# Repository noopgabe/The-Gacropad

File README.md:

# The GacroPad

> 

A six-key macro pad that plugs into a PC as a USB keyboard, with a small OLED for whatever you feel like showing it. Time, stats, whatever. If it doesn't have it, make it.

I made this because I play Roblox. Roblox is very weird. Some games are intense, and some are calmer. If you couldn't tell, I play intensely. I also listen to music. Can you REALLY switch between music and being in the middle of a chase sequence? No. No you can't. This is why I built the GacroPad. I also need macros for some things, limited to, but not excluding:

- Complicated actions 
- Die of Death
- Soundboard

The screen helps in a way because I can see the time when I'm in a heavy chase and I can't hit F11 without getting myself hit in a chase.

---

The repo has two halves: the firmware that runs on the pad, and a GTK4 companion app. The pad is good itself. The companion app is the real business, but the firmware is where all the magic happens. The companion app is cooler, I swear on my life.

## The hardware

It's built around an **ESP32-S3-WROOM-1U**:

- a 1.3" SSD1306 128x64 I2C OLED (the address is probed at boot, so `0x3C` and `0x3D` both work)
- native USB, but \* 2: TinyUSB HID for the keyboard and media keys, and a CDC port for talking to the companion app.

Macros can send ordinary keystrokes, raw HID usages, media keys, text, and delays. They're stored in NVS, so they survive power cycles and reflashes. If that is one of your worries, let them be free!

## Building the firmware

```bash
pio run
```

That gives you `firmware.bin`, which is only the application. A _first_ flash over the ROM bootloader kinda needs the whole thing, so instead run this:

```bash
pio run -t mergedbin
```

That writes `.pio/build/gacropad/gacropad.bin`, which includes the bootloader, partition table, and app, ready to flash at offset `0x0`.

### Flashing

There's buttons. On the PCB. One is BOOT. One is RESET. Hold BOOT, and then hit RESET. After, you can flash it through various ways, but my favorite is esptool. For the sake of time, I will only place that.

```bash
esptool.py --port /dev/ttyUSB0 write_flash 0x0 .pio/build/gacropad/gacropad.bin
```

## The companion app

GTK4, via PyGObject, which means it wants the system Python:

```bash
sudo apt install python3-gi gir1.2-gtk-4.0
pip install -r companion/requirements.txt
cd companion && /usr/bin/python3 main.py
```

A plain venv usually won't have `gi`, which is why we have the `/usr/bin/python3`. The app finds the pad on its own if there's only one, and you should only have one anyway, since 2 is nuts and 3 is a mental health issue.

What it's for:

- Macro editing. Seriously, what else? Click a key to open its editor. Recording captures whatever you do but only while the editor window has focus, because why else? Just write it down on a notepad if you need to remember. This is why it works on Wayland without root. Esc stops. There's a "test fire" button, and presets if you're a baby and you don't like to record.
- OLED modes. `labels` (key names), `clock`, `stats` (CPU and memory), and `live` (two lines of text you control). The live lines are plain text pushed over serial, so anything can be there.

The key buttons push one slot at a time, meanwhile "push all" pushes all six. Of course.

## The serial protocol

Newline-delimited JSON, one request per line, one reply per line. If you're handy, this is maybe useful. _Maybe._ This usually isn't, but if you eventually figure it out, congratulations, you're a nerd.

```
{"cmd":"ping"}
{"cmd":"get","key":0}
{"cmd":"set","key":0,"slot":{"label":"K1","steps":[{"t":"raw","v":104,"hold":40}]}}
{"cmd":"press","key":0}
{"cmd":"oled","mode":"clock"}
{"cmd":"live","clock":"14:32","l1":"hello","l2":"world"}
{"cmd":"stats","cpu":12,"mem":40}
{"cmd":"reset"}
```

Replies always carry `ok`, and an `err` when it's false. The pad also emits unsolicited `{"ev":...}` lines of its own when you press a key.

Macro steps are `delay`, `text`, `media`, `raw`, `key`, `down`, and `up`, where `down` and `up` are for chords, like holding Ctrl and then tapping C.

## CAD files

Well, here's the thing. The case is not done yet. It will be done soon. Trust me, it won't be late. 

## Credits and confessions

Built with [U8g2](https://github.com/olikraus/u8g2) (thank you) and [ArduinoJson](https://github.com/bblanchon/ArduinoJson) (thank you too), and a great deal of beating the hugs out of the ESP32 Arduino HID API until it worked well.

The code comments are better than the actual code, unfortunately. I am not good at programming, or designing, or whatever. If you object, do not.

I have committed many sins (sloth, sloth, sloth, and sloth), and this is unfortunately my penance. This was lazy, but that's fine.

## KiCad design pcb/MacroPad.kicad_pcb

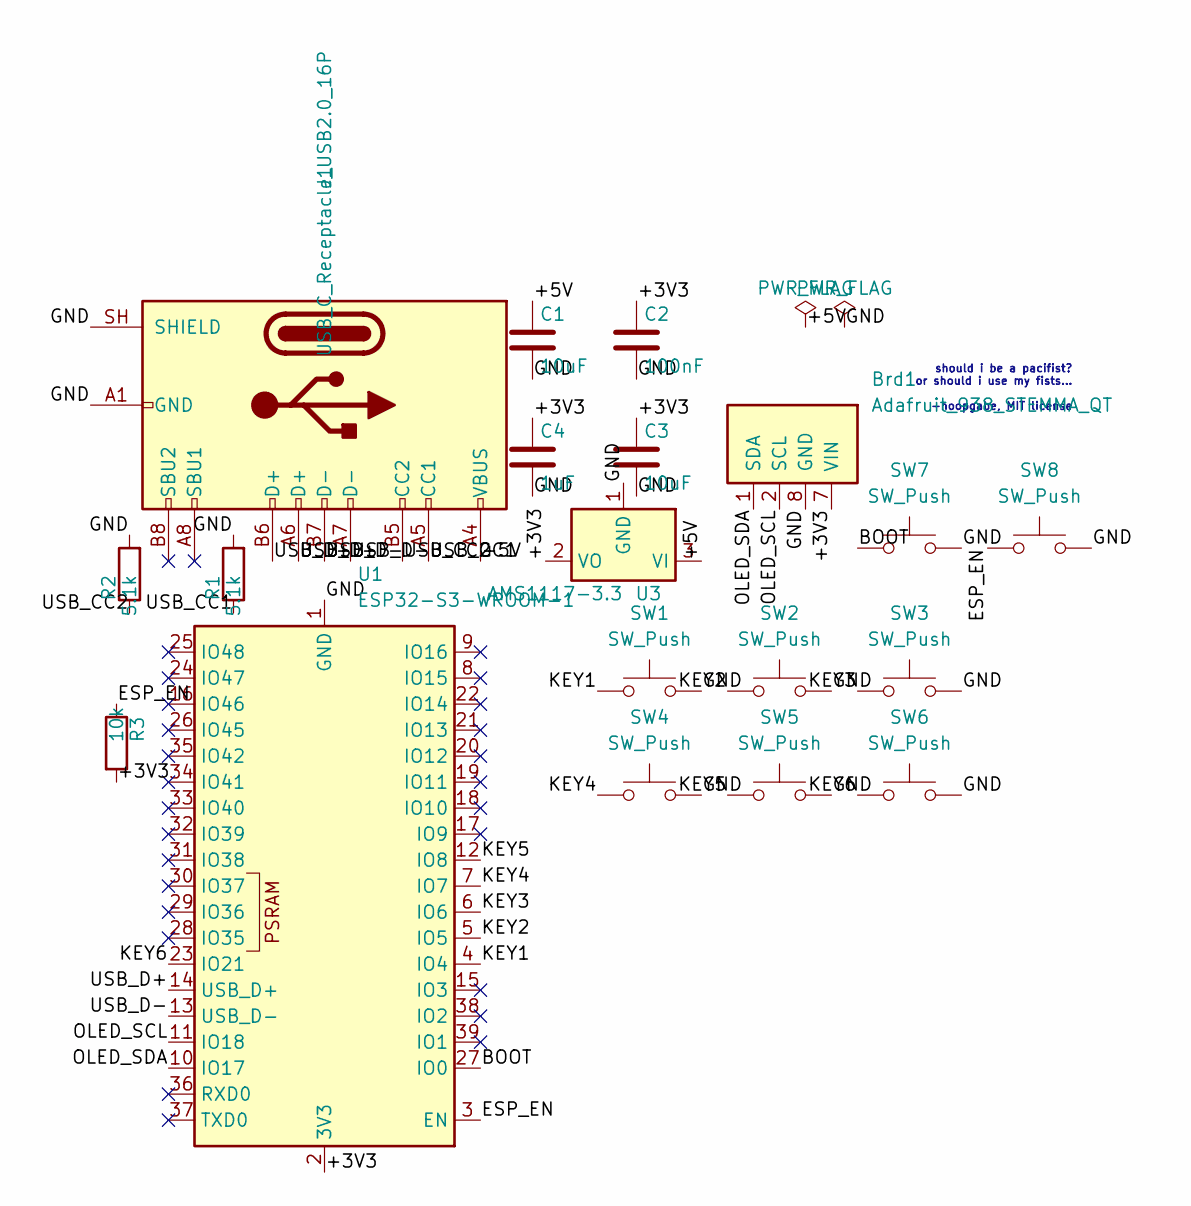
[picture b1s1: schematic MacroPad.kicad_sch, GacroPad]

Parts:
Brd1: Adafruit_938_STEMMA_QT
C1, C3: 10uF; C_0805_2012Metric
C2: 100nF; C_0603_1608Metric
C4: 1uF; C_0603_1608Metric
J1: USB_C_Receptacle_USB2.0_16P; USB_C_Receptacle_HRO_TYPE-C-31-M-12
R1, R2: 5.1k; R_0603_1608Metric
R3: 10k; R_0603_1608Metric
SW1, SW2, SW3, SW4, SW5, SW6: SW_Push; SW_Cherry_MX_1.00u_PCB
SW7, SW8: SW_Push; SW_PUSH_6mm_H5mm
U1: ESP32-S3-WROOM-1; ESP32-S3-WROOM-1U
U3: AMS1117-3.3; SOT-223-3_TabPin2; MPN AMS1117-3.3

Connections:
/+3V3: Brd1.7 (VIN), C2.1, C3.1, C4.1, R3.2, U1.2 (3V3), U3.2 (VO)
/+5V: C1.1, J1.A4 (VBUS), J1.A9 (VBUS), J1.B4 (VBUS), J1.B9 (VBUS), U3.3 (VI)
/BOOT: SW7.1, U1.27 (IO0)
/ESP_EN: R3.1, SW8.1, U1.3 (EN)
/GND: Brd1.8 (GND), C1.2, C2.2, C3.2, C4.2, J1.A1 (GND), J1.A12 (GND), J1.B1 (GND), J1.B12 (GND), J1.SH (SHIELD), R1.2, R2.2, SW1.2, SW2.2, SW3.2, SW4.2, SW5.2, SW6.2, SW7.2, SW8.2, U1.1 (GND), U1.40 (GND), U1.41 (GND), U3.1 (GND)
/KEY1: SW1.1, U1.4 (IO4)
/KEY2: SW2.1, U1.5 (IO5)
/KEY3: SW3.1, U1.6 (IO6)
/KEY4: SW4.1, U1.7 (IO7)
/KEY5: SW5.1, U1.12 (IO8)
/KEY6: SW6.1, U1.23 (IO21)
/OLED_SCL: Brd1.2 (SCL), U1.11 (IO18)
/OLED_SDA: Brd1.1 (SDA), U1.10 (IO17)
/USB_CC1: J1.A5 (CC1), R1.1
/USB_CC2: J1.B5 (CC2), R2.1
/USB_D+: J1.A6 (D+), J1.B6 (D+), U1.14 (USB_D+)
/USB_D-: J1.A7 (D-), J1.B7 (D-), U1.13 (USB_D-)

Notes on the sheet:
should i be a pacifist? or should i use my fists... -noopgabe, MIT license

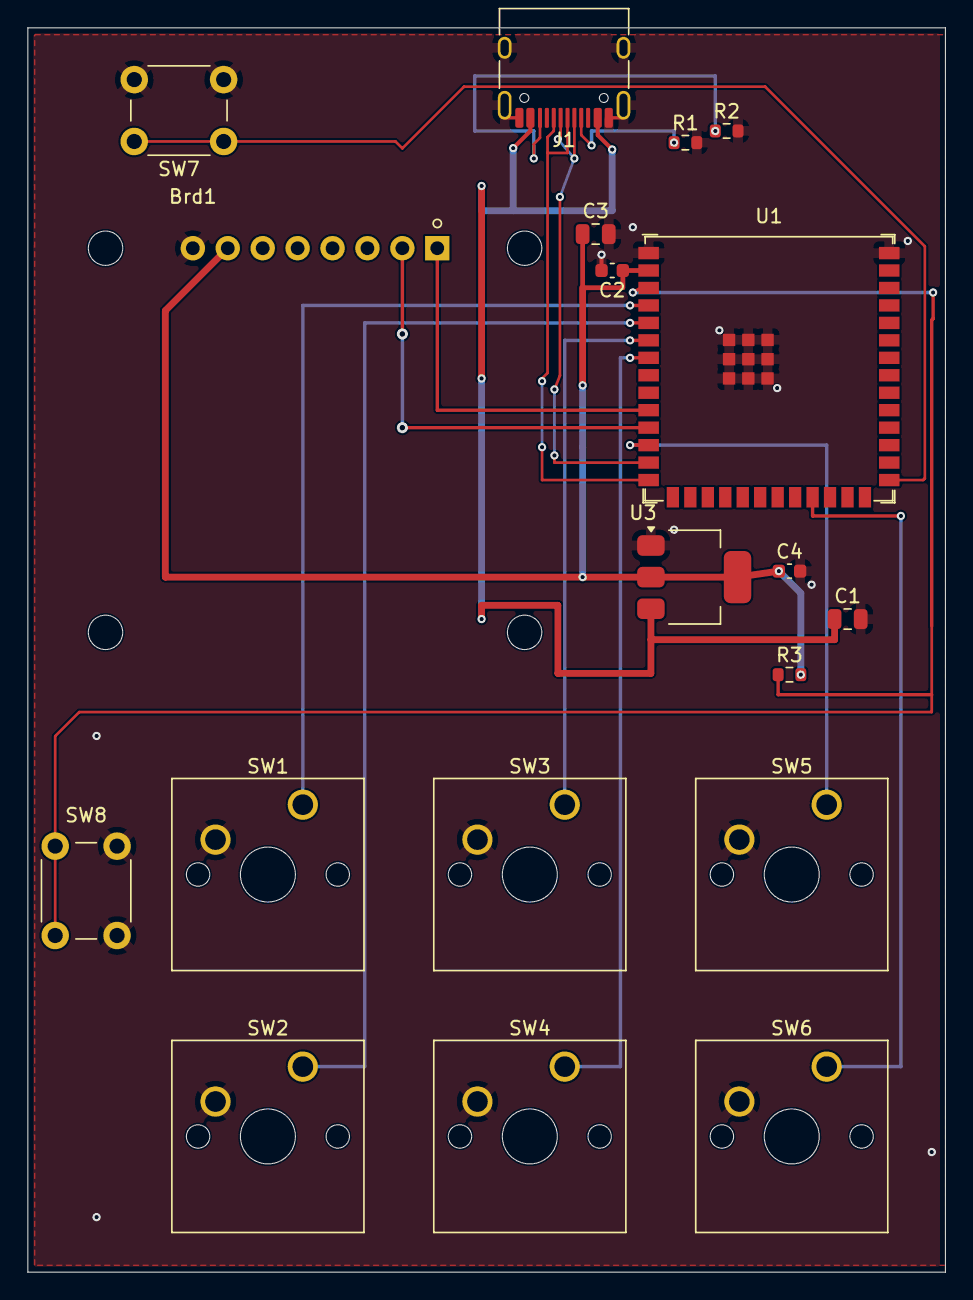
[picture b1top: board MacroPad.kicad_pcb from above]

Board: 2 copper layers, 66.7 x 90.5 mm, 19 parts (0 on the bottom side), 17 nets.

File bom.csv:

Item Name,Qty,Price (total) (USD),Item link,Notes
ESP32-S3-WROOM-1U-N8,1,4.54,https://www.lcsc.com/product-detail/C2980297.html,
USB-C receptacle,5,0.86,https://www.lcsc.com/product-detail/C165948.html,
10kΩ resistor,100,0.39,https://www.lcsc.com/product-detail/C965184.html,
AMS1117-3.3,5,1.05,https://www.lcsc.com/product-detail/C6186.html,
Tactile button,5,0.76,https://www.lcsc.com/product-detail/C722171.html,
10uF capacitor,20,1.31,https://www.lcsc.com/product-detail/C15850.html,
100nF capacitor,50,0.62,https://www.lcsc.com/product-detail/C14663.html,
1uF capacitor,20,0.5,https://www.lcsc.com/product-detail/C106858.html,
5.1kΩ resistor,100,0.15,https://www.lcsc.com/product-detail/C23186.html,
LCSC shipping + handling,N/A,11.32,N/A,standard shipping
JLC manufacturing + shipping,5,$7.38,N/A,ditto
Adafruit oled,1,19.95,https://www.digikey.com/en/products/detail/adafruit-industri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,
DigiKey shipping,N/A,4.99,N/A,standard usps ground advantage
Soldering iron,1,$10.64,https://a.co/d/09gOBPuw,i have prime so its okie-dokie
,,,,
,,,,
,,,,
,,,,
,,,,
Total Price (USD):,64.46,,,
